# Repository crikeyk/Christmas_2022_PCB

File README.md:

# Christmas ornament PCB 2022

A small project to refine my PCB design and C programming skills

## Front View

## Rear view

## Perspective view

## Routed PCB

## Unpopulated PCB

## Final Product

## "Production run"

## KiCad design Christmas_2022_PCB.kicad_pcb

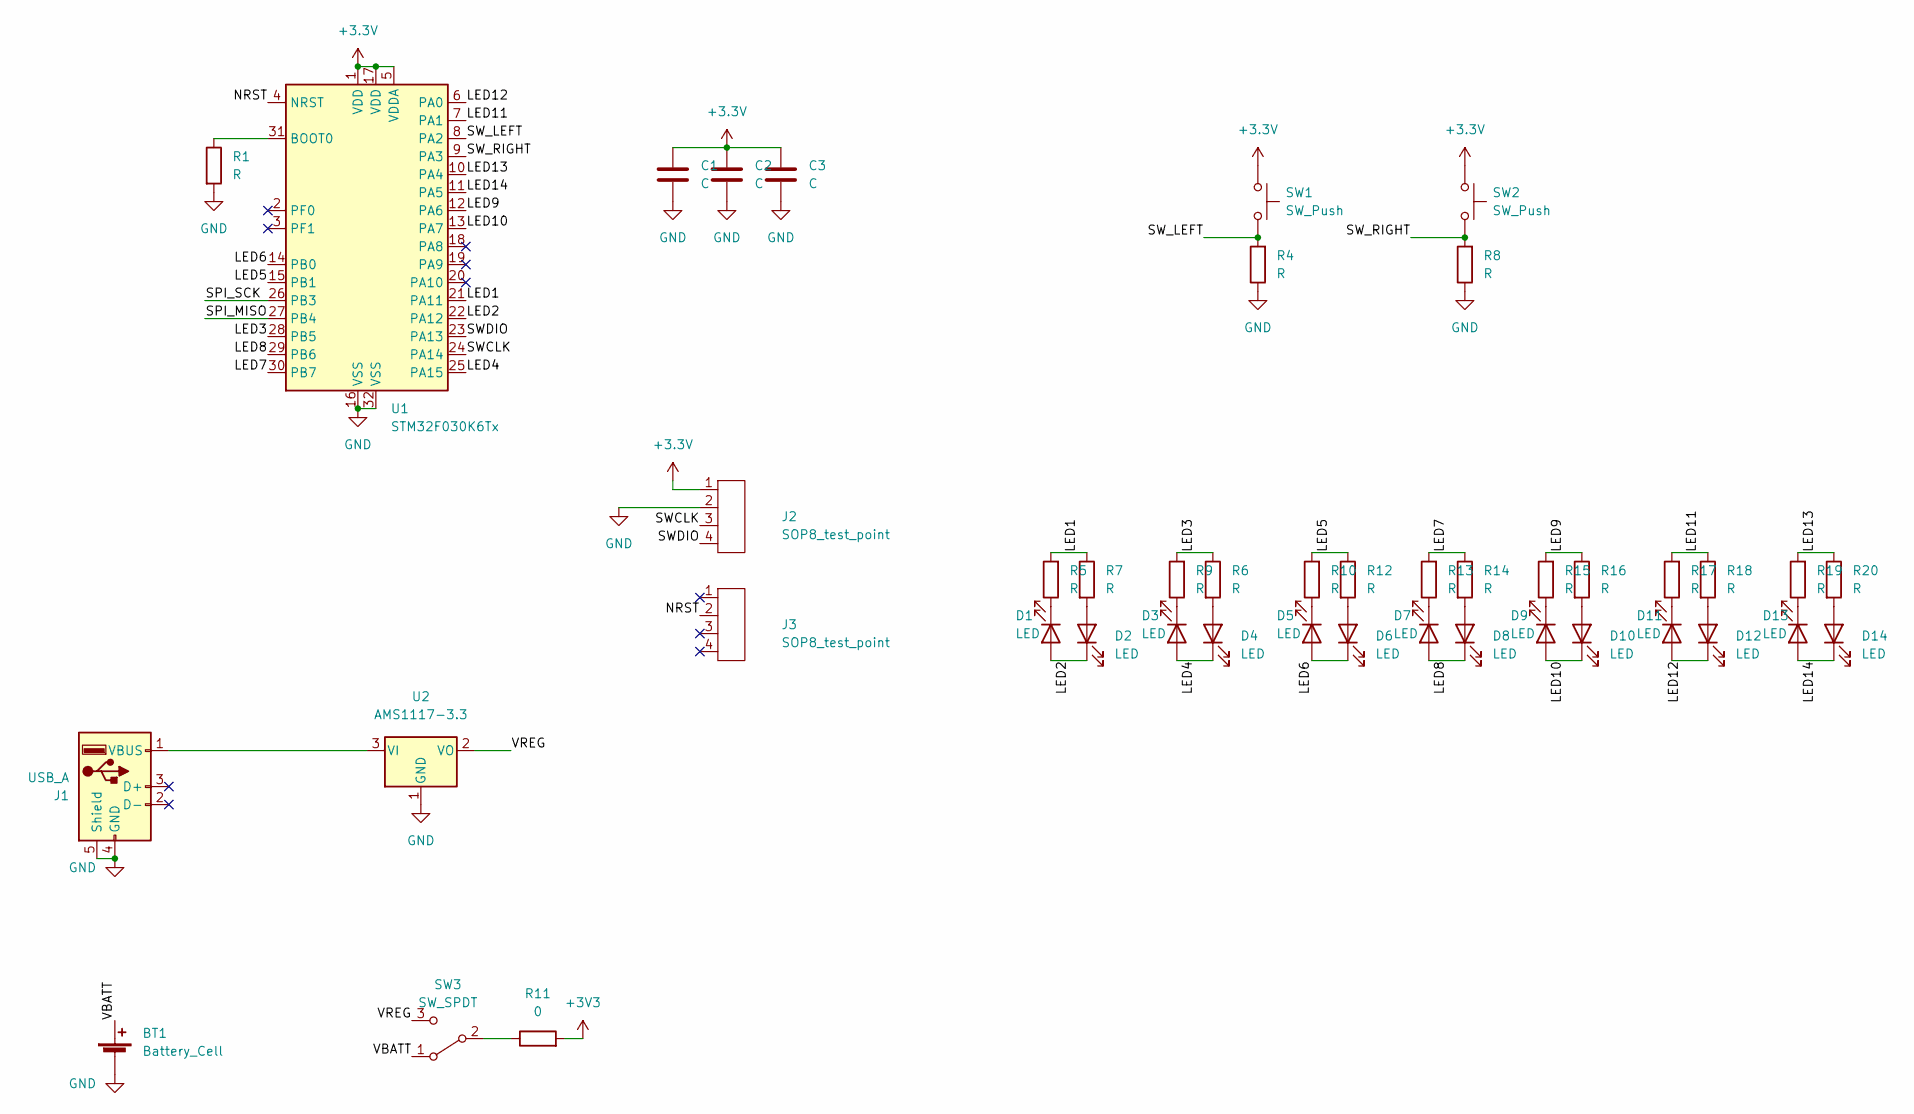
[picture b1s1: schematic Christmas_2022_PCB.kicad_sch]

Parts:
BT1: Battery_Cell; BatteryHolder_Keystone_3034_1x20mm
C1, C2, C3: C; C_0805_2012Metric_Pad1.18x1.45mm_HandSolder
D1, D2, D3, D4, D5, D6, D7, D8, D9, D10, D11, D12, D13, D14: LED; LED_0805_2012Metric_Pad1.15x1.40mm_HandSolder
J1: USB_A; USB_A_CNCTech_1001-011-01101_Horizontal
J2, J3: SOP8_test_point; sop_8_test_pad
R1, R4, R5, R6, R7, R8, R9, R10, R12, R13, R14, R15, R16, R17, R18, R19, R20: R; R_0805_2012Metric_Pad1.20x1.40mm_HandSolder
R11: 0; R_0805_2012Metric_Pad1.20x1.40mm_HandSolder
SW1, SW2: SW_Push; 3_6_2_5mm_push_button_G_lead
SW3: SW_SPDT; SW_SPDT_PCM12
U1: STM32F030K6Tx; LQFP-32_7x7mm_P0.8mm
U2: AMS1117-3.3; SOT-223-3_TabPin2

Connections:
/LED1: R5.2, R7.1, U1.21 (PA11)
/LED2: D1.2 (A), D2.1 (K), U1.22 (PA12)
/LED3: R6.1, R9.2, U1.28 (PB5)
/LED4: D3.2 (A), D4.1 (K), U1.25 (PA15)
/LED5: R10.2, R12.1, U1.15 (PB1)
/LED6: D5.2 (A), D6.1 (K), U1.14 (PB0)
/LED7: R13.2, R14.1, U1.30 (PB7)
/LED8: D7.2 (A), D8.1 (K), U1.29 (PB6)
/LED9: R15.2, R16.1, U1.12 (PA6)
/LED10: D9.2 (A), D10.1 (K), U1.13 (PA7)
/LED11: R17.2, R18.1, U1.7 (PA1)
/LED12: D11.2 (A), D12.1 (K), U1.6 (PA0)
/LED13: R19.2, R20.1, U1.10 (PA4)
/LED14: D13.2 (A), D14.1 (K), U1.11 (PA5)
/NRST: J3.2, U1.4 (NRST)
/SPI_MISO: U1.27 (PB4)
/SPI_SCK: U1.26 (PB3)
/SWCLK: J2.3, U1.24 (PA14)
/SWDIO: J2.4, U1.23 (PA13)
/SW_LEFT: R4.2, SW1.2, U1.8 (PA2)
/SW_RIGHT: R8.2, SW2.2, U1.9 (PA3)
/VBATT: BT1.1 (+), SW3.1 (A)
/VREG: SW3.3 (C), U2.2 (VO)
GND: BT1.2 (-), C1.2, C2.2, C3.2, J1.4 (GND), J1.5 (Shield), J2.2, R1.2, R4.1, R8.1, U1.16 (VSS), U1.32 (VSS), U2.1 (GND)
unnamed: D1.1 (K), R5.1
unnamed: D2.2 (A), R7.2
unnamed: D3.1 (K), R9.1
unnamed: D4.2 (A), R6.2
unnamed: D5.1 (K), R10.1
unnamed: D6.2 (A), R12.2
unnamed: D7.1 (K), R13.1
unnamed: D8.2 (A), R14.2
unnamed: D9.1 (K), R15.1
unnamed: D10.2 (A), R16.2
unnamed: D11.1 (K), R17.1
unnamed: D12.2 (A), R18.2
unnamed: D13.1 (K), R19.1
unnamed: D14.2 (A), R20.2
unnamed: J1.1 (VBUS), U2.3 (VI)
unnamed: R1.1, U1.31 (BOOT0)
unnamed: R11.1, SW3.2 (B)

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
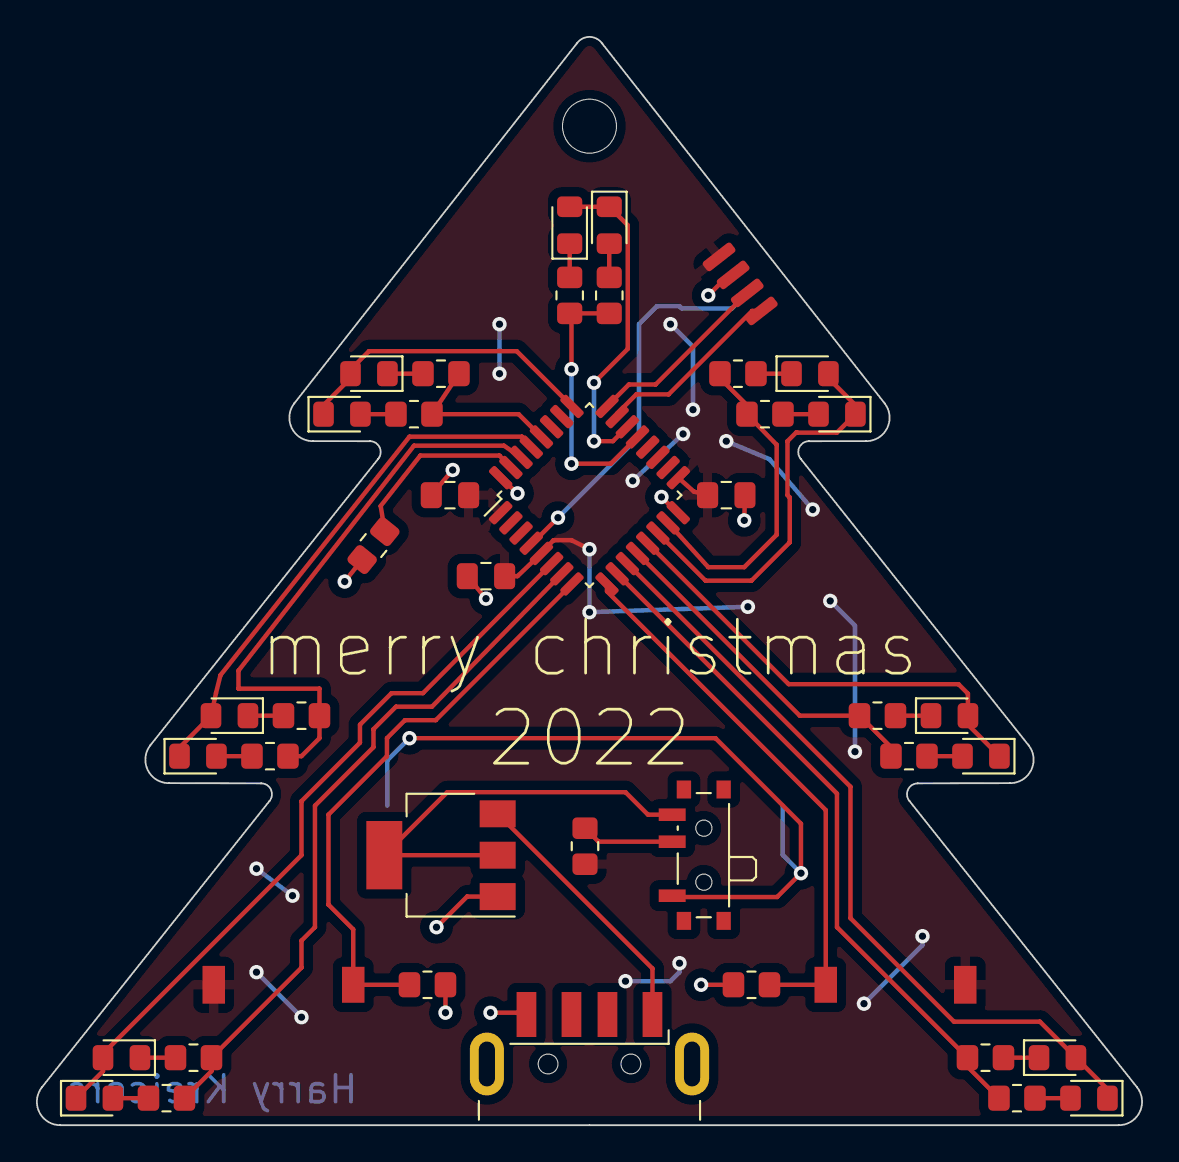
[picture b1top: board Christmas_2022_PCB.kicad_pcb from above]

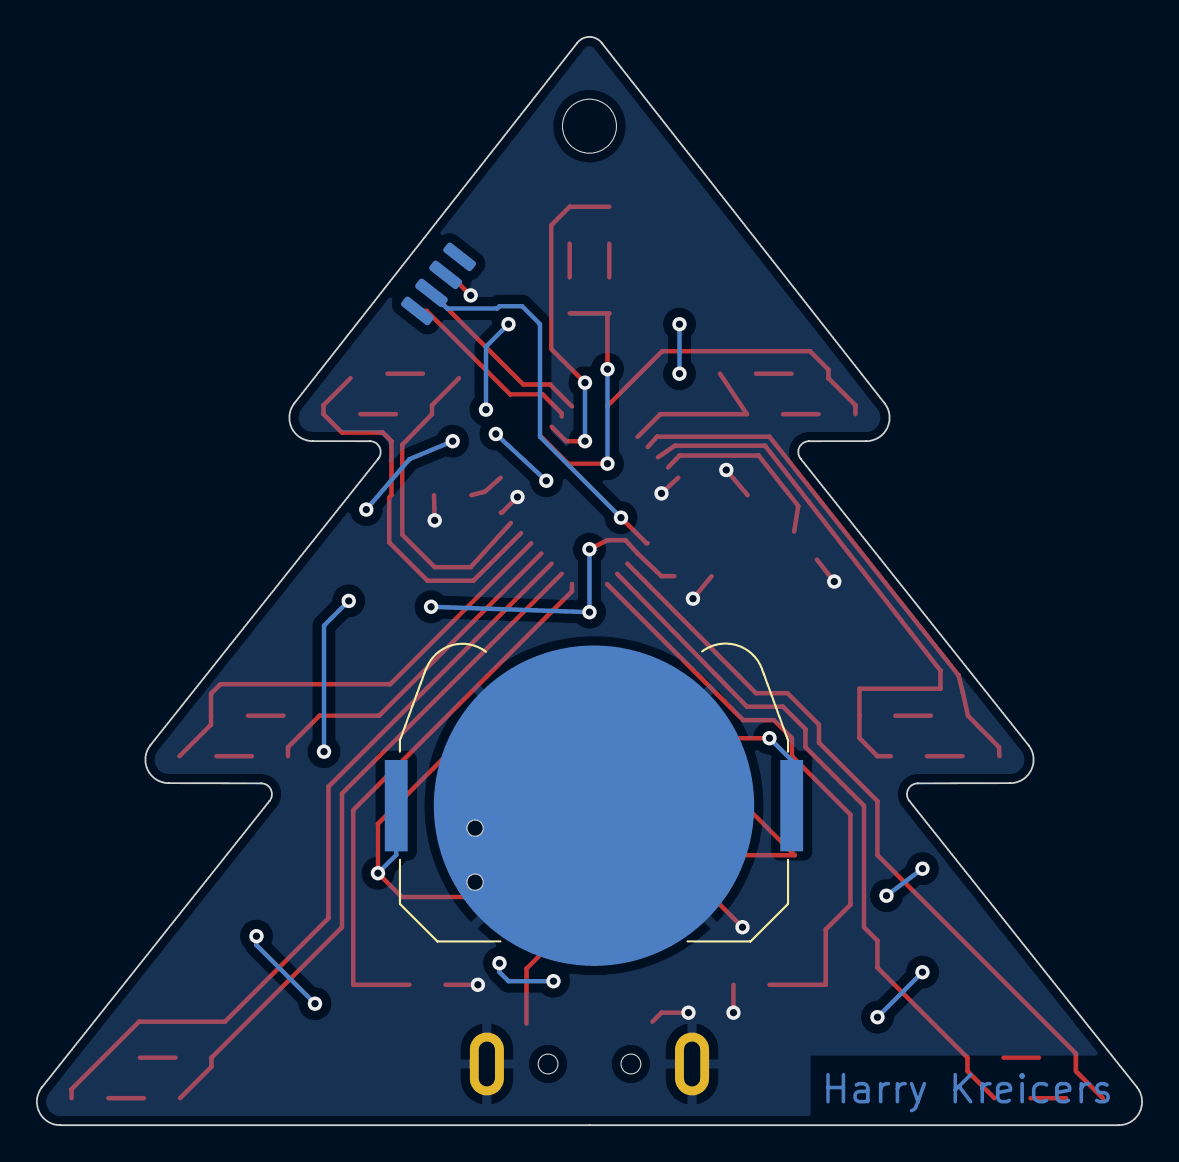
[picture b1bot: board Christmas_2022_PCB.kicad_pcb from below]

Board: 2 copper layers, 61.4 x 60.5 mm, 45 parts (2 on the bottom side), 40 nets.

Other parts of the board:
TH1: MountingHole_3mm

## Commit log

2022-09-03 initialised PCB
2022-09-04 Added 3.3V slide switch
2022-09-05 initial board outline added
2022-09-06 began component placement
2022-09-06 completed initial layout
2022-09-07 began routing
2022-09-08 Added secondary LEDs
2022-09-09 finished routing. Added missing 3D models
2022-09-10 modified VCC pour to balance copper
2022-09-10 Finished routing. Output gerbers and drill files
2022-09-10 Added images dir and updated README
2022-09-10 Fixed README image alignment
2022-09-12 associated 3D model with tracked file
